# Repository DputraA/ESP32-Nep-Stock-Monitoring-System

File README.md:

# ESP32 Nepel Stock Monitoring System

Sistem monitoring persediaan nepel berbasis ESP32, multiplexer (MUX), dan web server lokal, dengan fitur pengiriman data ke Google Sheets dan tampilan real-time status melalui halaman web. Sistem ini digunakan untuk mendeteksi apakah stok nepel tersedia (`ready`) atau habis (`runout`), dan mencatat log perubahan status serta uptime WiFi ESP32.

---

## Fitur Utama

- Monitoring hingga 4 channel sensor digital (bisa diperluas)
- Deteksi perubahan status sensor secara otomatis
- Pengiriman data ke Google Spreadsheet via WebScript
- Webserver lokal dengan tampilan status dan log
- Fitur uptime monitoring (timer berjalan jika WiFi aktif)
- Auto-refresh dashboard jika ada perubahan
- Log maksimal 10 perubahan terakhir ditampilkan di halaman web
- Auto-reconnect jika WiFi terputus

---

## Struktur Proyek

File utama:
- `main.ino`= file kode utama ESP32
- `README.md`= dokumentasi ini
- 'Appscript for Spreadsheet.json' = Appscript penghubung ke spreadsheet
- 'Dashboard monitoring stock nepel.html' = Auto redirect ke halaman webserver
---

## Tampilan Webserver

Dashboard lokal menampilkan:
- Status semua channel (warna hijau = ready, merah = runout)
- Timestamp update terakhir setiap channel
- Log perubahan terakhir
- Uptime dari koneksi WiFi

---

##  Cara Upload dan Jalankan

1. Buka file `.ino` dengan Arduino IDE
2. Pastikan library berikut sudah tersedia:
   - `WiFi.h`
   - `WebServer.h`
   - `HTTPClient.h`
   - `ArduinoJson.h`
   - `time.h`
3. Atur:
   - `ssid` dan `password` sesuai WiFi lokal
   - `scriptURL` sesuai link Google Apps Script Anda
4. Upload ke ESP32
5. Buka file 'Dashboard monitoring stock nepel.html' di browser

---

## Menambah Channel Sensor

Secara default, sistem membaca 4 channel (`totalChannels = 4`). Untuk menambah jumlah channel:

1. Ubah variabel `totalChannels`:
  	 ```cpp
  	 const int totalChannels = 8;
2. Update array namaNepel[] agar mencakup semua channel baru:

 	  ```cpp
	const char* namaNepel[totalChannels] = {
	"Nepel 12-12", "Nepel 12-10", "Nepel 10-10", "Nepel Single 10",
	"Nepel Extra 1", "Nepel Extra 2", "Nepel Extra 3", "Nepel Extra 4"
	};
3. (Opsional) Aktifkan multiplexer kedua/ketiga jika total channel melebihi 8 atau 16:

	```cpp
	digitalWrite(muxEN1, LOW);  // Channel 0–7
	digitalWrite(muxEN2, LOW);  // Channel 8–15 (MUX 2)
	digitalWrite(muxEN3, LOW);  // Channel 16–23 (MUX 3)

## Mengganti Nama Channel
1. Edit isi array namaNepel[] sesuai urutan channel:

	```cpp
	const char* namaNepel[totalChannels] = {
	  "Nepel A", "Nepel B", "Nepel C", "Nepel D"
	};

2. Nama ini akan digunakan untuk:

- Label log di spreadsheet

- Tampilan web dashboard

- JSON yang dikirim ke Google Sheets

## Membuka Webserver Menggunakan redirect `.html`

Agar lebih mudah mengakses IP lokal ESP32 tanpa mengetik alamat IP manual, gunakan file Redirect `Dashboard monitoring stock nepel.html`.

## Catatan Tambahan
Tempat penyimpanan fisik saat ini hanya mampu menampung 4 jenis material nepel dan menggunakan impraboard.
Disarankan untuk mengganti tempat penyimpanan ke bahan stainless steel agar lebih kuat, awet, dan cocok digunakan di lingkungan pabrik.
Pastikan power supply memberikan tegangan 5V stabil ke ESP32, dan 24V untuk sensor serta pilot lamp.

## Lisensi
Proyek ini bersifat open-source dan bebas digunakan untuk edukasi dan pengembangan lebih lanjut.

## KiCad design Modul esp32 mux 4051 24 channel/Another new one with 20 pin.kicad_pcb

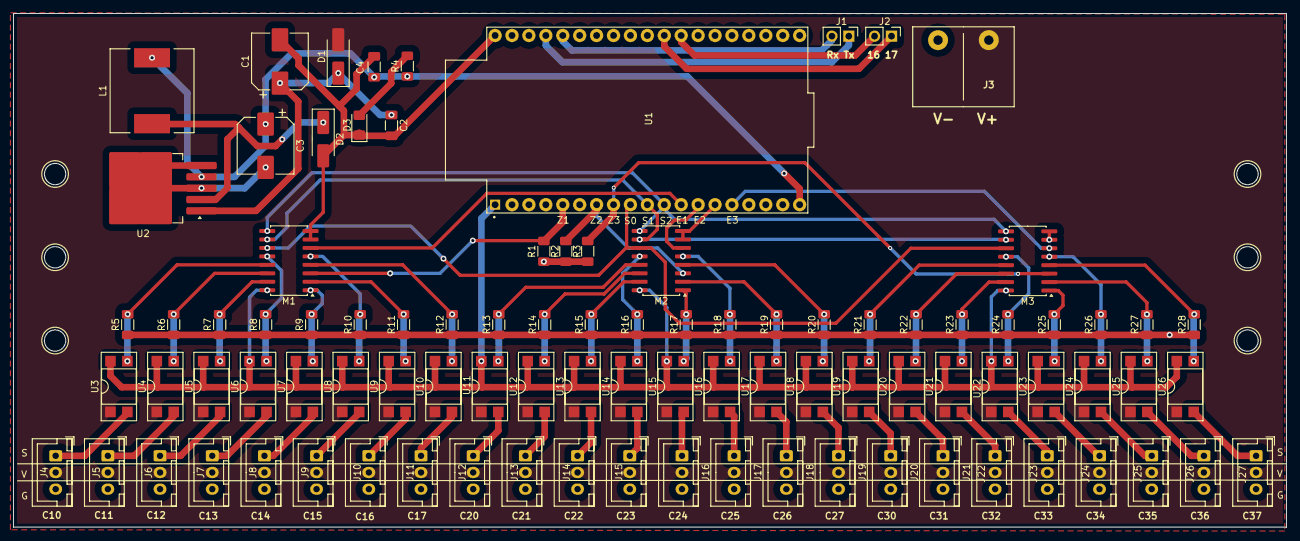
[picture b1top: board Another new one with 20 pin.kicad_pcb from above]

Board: 2 copper layers, 191.1 x 77.1 mm, 92 parts (0 on the bottom side), 68 nets.

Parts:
C1, C3: 220uF; CP_Elec_8x10
C2, C4: 100nF; C_1206_3216Metric_Pad1.33x1.80mm_HandSolder
D1, D2: SS14; D_SMA_Handsoldering
D3: LED; LED_1206_3216Metric_Pad1.42x1.75mm_HandSolder
J1, J2: Conn_01x02_Socket; PinHeader_1x02_P2.54mm_Vertical
J3: Screw_Terminal_01x02; KF7.62_2P
J4, J5, J6, J7, J8, J9, J10, J11, J12, J13, J14, J15, J16, J17, J18, J19, J20, J21, J22, J23, J24, J25, J26, J27: Conn_01x03_Pin; JST_XH_B3B-XH-A_1x03_P2.50mm_Vertical
L1: 68uH; L_12x12mm_H8mm
M1, M2, M3: 74HC4051; SOIC-16W_5.3x10.2mm_P1.27mm
R1, R2, R3, R5, R6, R7, R8, R9, R10, R11, R12, R13, R14, R15, R16, R17, R18, R19, R20, R21, R22, R23, R24, R25, R26, R27, R28: R; R_1206_3216Metric_Pad1.30x1.75mm_HandSolder
R4: 1K; R_1206_3216Metric_Pad1.30x1.75mm_HandSolder
U1: ESP32-DEVKITC-v4; MODULE_ESP32-DEVKITC
U2: LM2596S-5; TO-263-5_TabPin3
U3, U4, U5, U6, U7, U8, U9, U10, U11, U12, U13, U14, U15, U16, U17, U18, U19, U20, U21, U22, U23, U24, U25, U26: PC817; DIP-4_W7.62mm_SMDSocket_SmallPads

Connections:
/Buck Converter 24 to 5/GND: C1.2, C2.2, C3.2, C4.2, D2.2 (A), D3.1 (K), J3.2, J4.3, J5.3, J6.3, J7.3, J8.3, J9.3, J10.3, J11.3, J12.3, J13.3, J14.3, J15.3, J16.3, J17.3, J18.3, J19.3, J20.3, J21.3, J22.3, J23.3, J24.3, J25.3, J26.3, J27.3, M1.7 (VEE), M1.8 (GND), M2.7 (VEE), M2.8 (GND), M3.7 (VEE), M3.8 (GND), R1.1, R2.1, R3.1, R5.1, R6.1, R7.1, R8.1, R9.1, R10.1, R11.1, R12.1, R13.1, R14.1, R15.1, R16.1, R17.1, R18.1, R19.1, R20.1, R21.1, R22.1, R23.1, R24.1, R25.1, R26.1, R27.1, R28.1, U1.14 (GND1), U1.32 (GND2), U1.38 (GND3), U2.3 (GND), U2.5 (~ON/OFF)
/Buck Converter 24 to 5/IN: D1.2 (A), J3.1, J4.2, J5.2, J6.2, J7.2, J8.2, J9.2, J10.2, J11.2, J12.2, J13.2, J14.2, J15.2, J16.2, J17.2, J18.2, J19.2, J20.2, J21.2, J22.2, J23.2, J24.2, J25.2, J26.2, J27.2, U3.1, U4.1, U5.1, U6.1, U7.1, U8.1, U9.1, U10.1, U11.1, U12.1, U13.1, U14.1, U15.1, U16.1, U17.1, U18.1, U19.1, U20.1, U21.1, U22.1, U23.1, U24.1, U25.1, U26.1
/Buck Converter 24 to 5/OUT (5V): C3.1, C4.1, L1.2, R4.1, U1.19 (EXT_5V), U2.4 (FB)
/Multiplexer/1: J4.1, U3.2
/Multiplexer/2: J5.1, U4.2
/Multiplexer/3: J6.1, U5.2
/Multiplexer/3.3v: M1.16 (VCC), M2.16 (VCC), M3.16 (VCC), U1.1 (3V3), U3.4, U4.4, U5.4, U6.4, U7.4, U8.4, U9.4, U10.4, U11.4, U12.4, U13.4, U14.4, U15.4, U16.4, U17.4, U18.4, U19.4, U20.4, U21.4, U22.4, U23.4, U24.4, U25.4, U26.4
/Multiplexer/4: J7.1, U6.2
/Multiplexer/5: J8.1, U7.2
/Multiplexer/6: J9.1, U8.2
/Multiplexer/7: J10.1, U9.2
/Multiplexer/8: J11.1, U10.2
/Multiplexer/9: J12.1, U11.2
/Multiplexer/10: J13.1, U12.2
/Multiplexer/11: J14.1, U13.2
/Multiplexer/12: J15.1, U14.2
/Multiplexer/13: J16.1, U15.2
/Multiplexer/14: J17.1, U16.2
/Multiplexer/15: J18.1, U17.2
/Multiplexer/16: J19.1, U18.2
/Multiplexer/17: J20.1, U19.2
/Multiplexer/18: J21.1, U20.2
/Multiplexer/19: J22.1, U21.2
/Multiplexer/20: J23.1, U22.2
/Multiplexer/21: J24.1, U23.2
/Multiplexer/22: J25.1, U24.2
/Multiplexer/23: J26.1, U25.2
/Multiplexer/24: J27.1, U26.2
/Multiplexer/En1: M1.6 (~E), U1.12 (IO14)
/Multiplexer/En2: M2.6 (~E), U1.13 (IO12)
/Multiplexer/En3: M3.6 (~E), U1.15 (IO13)
/Multiplexer/Out1: M1.3 (A), R1.2, U1.5 (IO34)
/Multiplexer/Out2: M2.3 (A), R2.2, U1.7 (IO32)
/Multiplexer/Out3: M3.3 (A), R3.2, U1.8 (IO33)
/Multiplexer/S0: M1.11 (S0), M2.11 (S0), M3.11 (S0), U1.9 (IO25)
/Multiplexer/S1: M1.10 (S1), M2.10 (S1), M3.10 (S1), U1.10 (IO26)
/Multiplexer/S2: M1.9 (S2), M2.9 (S2), M3.9 (S2), U1.11 (IO27)
unnamed: C1.1, C2.1, D1.1 (K), U2.1 (VIN)
unnamed: D2.1 (K), L1.1, U2.2 (OUT)
unnamed: D3.2 (A), R4.2
unnamed: J1.1, U1.35 (TXD0)
unnamed: J1.2, U1.34 (RXD0)
unnamed: J2.1, U1.28 (IO17)
unnamed: J2.2, U1.27 (IO16)
unnamed: M1.13 (A0), R5.2, U3.3
unnamed: M1.14 (A1), R6.2, U4.3
unnamed: M1.15 (A2), R7.2, U5.3
unnamed: M1.12 (A3), R8.2, U6.3
unnamed: M1.1 (A4), R9.2, U7.3
unnamed: M1.5 (A5), R10.2, U8.3
unnamed: M1.2 (A6), R11.2, U9.3
unnamed: M1.4 (A7), R12.2, U10.3
unnamed: M2.13 (A0), R13.2, U11.3
unnamed: M2.14 (A1), R14.2, U12.3
unnamed: M2.15 (A2), R15.2, U13.3
unnamed: M2.12 (A3), R16.2, U14.3
unnamed: M2.1 (A4), R17.2, U15.3
unnamed: M2.5 (A5), R18.2, U16.3
unnamed: M2.2 (A6), R19.2, U17.3
unnamed: M2.4 (A7), R20.2, U18.3
unnamed: M3.13 (A0), R21.2, U19.3
unnamed: M3.14 (A1), R22.2, U20.3
unnamed: M3.15 (A2), R23.2, U21.3
unnamed: M3.12 (A3), R24.2, U22.3
unnamed: M3.1 (A4), R25.2, U23.3
unnamed: M3.5 (A5), R26.2, U24.3
unnamed: M3.2 (A6), R27.2, U25.3
unnamed: M3.4 (A7), R28.2, U26.3

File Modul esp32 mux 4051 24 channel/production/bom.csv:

Designator,Footprint,Quantity,Value,LCSC Part #
"C1, C3",CP_Elec_8x10,2,220uF,
"C2, C4",1206,2,100nF,
"D1, D2",D_SMA_Handsoldering,2,SS14,
D3,1206,1,LED,
"J1, J2",PinHeader_1x02_P2.54mm_Vertical,2,Conn_01x02_Socket,
"J10, J11, J12, J13, J14, J15, J16, J17, J18, J19, J20, J21, J22, J23, J24, J25, J26, J27, J4, J5, J6, J7, J8, J9",JST_XH_B3B-XH-A_1x03_P2.50mm_Vertical,24,Conn_01x03_Pin,
J3,KF7.62_2P,1,Screw_Terminal_01x02,
L1,L_12x12mm_H8mm,1,68uH,
"M1, M2, M3",SOIC-16W_5.3x10.2mm_P1.27mm,3,74HC4051,
"R1, R10, R11, R12, R13, R14, R15, R16, R17, R18, R19, R2, R20, R21, R22, R23, R24, R25, R26, R27, R28, R3, R5, R6, R7, R8, R9",1206,27,R,
R4,1206,1,1K,
U1,MODULE_ESP32-DEVKITC,1,ESP32-DEVKITC-v4,
"U10, U11, U12, U13, U14, U15, U16, U17, U18, U19, U20, U21, U22, U23, U24, U25, U26, U3, U4, U5, U6, U7, U8, U9",DIP-4_W7.62mm_SMDSocket_SmallPads,24,PC817,
U2,TO-263-5_TabPin3,1,LM2596S-5,

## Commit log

2025-07-29 Rename NepelHose_StockMonitoring_4of24Channel.ino to main
2025-07-29 Rename main to main.ino
2025-07-29 Rename main.ino to main/main.ino
